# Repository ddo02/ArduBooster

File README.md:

# ArduBooster
TODO: Write the readme!

ArduBooster repository.

# License
This project is under dual-license.

First license is for commercial use of this project. To build a product, based on this project, and sell it.

Second license is for non-commercial use of this project. To build a sample, to personal use or education use.

# Donate

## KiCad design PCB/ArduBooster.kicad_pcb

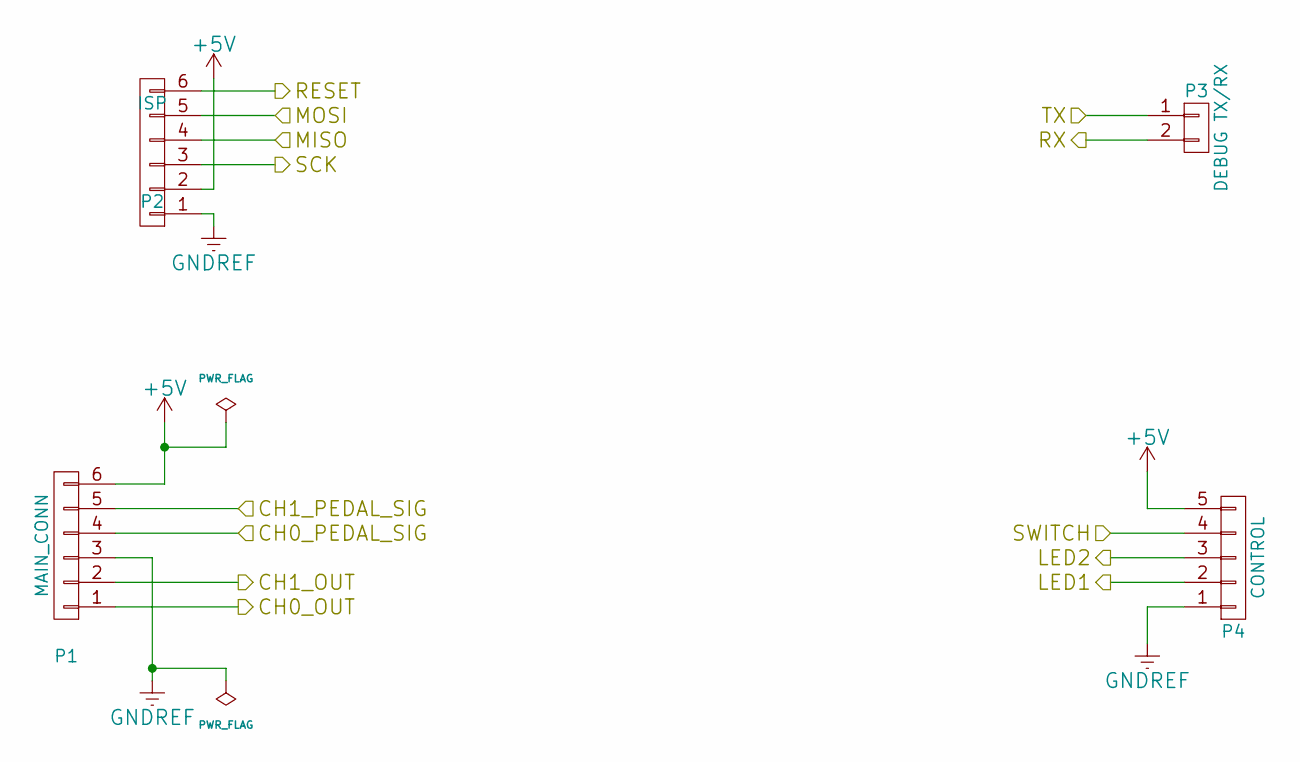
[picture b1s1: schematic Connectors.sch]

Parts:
P1: MAIN_CONN; Molex_MiniFit-JR-5569-06A1_2x03x4.20mm_Angled
P2: ISP; Pin_Header_Straight_1x06_Pitch2.54mm
P3: DEBUG TX/RX; Pin_Header_Straight_1x02_Pitch2.54mm
P4: CONTROL; Wafer_Horizontal15x5.8x7RM2.5-5

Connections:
+5V: P1.6, P2.2, P4.5; also elsewhere on the board
/Base Arduino/CH0_OUT: P1.1; also elsewhere on the board
/Base Arduino/CH0_PEDAL_SIG: P1.4; also elsewhere on the board
/Base Arduino/CH1_OUT: P1.2; also elsewhere on the board
/Base Arduino/CH1_PEDAL_SIG: P1.5; also elsewhere on the board
/Base Arduino/LED1: P4.2; also elsewhere on the board
/Base Arduino/LED2: P4.3; also elsewhere on the board
/Base Arduino/MISO: P2.4; also elsewhere on the board
/Base Arduino/MOSI: P2.5; also elsewhere on the board
/Base Arduino/RESET: P2.6; also elsewhere on the board
/Base Arduino/RX: P3.2; also elsewhere on the board
/Base Arduino/SCK: P2.3; also elsewhere on the board
/Base Arduino/SWITCH: P4.4; also elsewhere on the board
/Base Arduino/TX: P3.1; also elsewhere on the board
GNDREF: P1.3, P2.1, P4.1; also elsewhere on the board

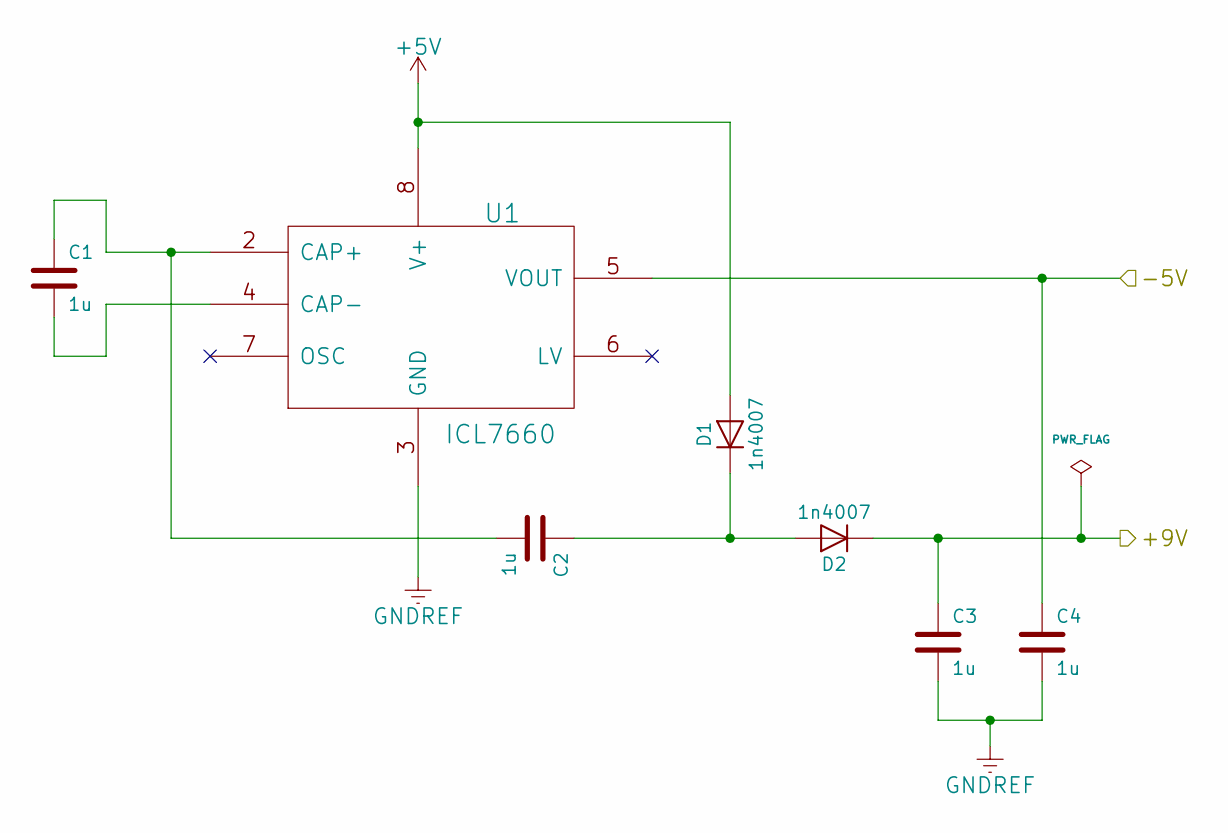
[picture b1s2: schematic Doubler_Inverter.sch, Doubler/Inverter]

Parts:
C1, C2, C3, C4: 1u; C_Rect_L7.0mm_W4.5mm_P5.00mm
D1, D2: 1n4007; D_A-405_P2.54mm_Vertical_AnodeUp
U1: ICL7660; DIP-8_W7.62mm_LongPads

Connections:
+5V: D1.2 (A), U1.8 (V+); also elsewhere on the board
/Doubler_Inverter/+9V: C3.1, D2.1 (K); also elsewhere on the board
/Doubler_Inverter/-5V: C4.1, U1.5 (VOUT); also elsewhere on the board
GNDREF: C3.2, C4.2, U1.3 (GND); also elsewhere on the board
unnamed: C1.1, C2.2, U1.2 (CAP+)
unnamed: C1.2, U1.4 (CAP-)
unnamed: C2.1, D1.1 (K), D2.2 (A)

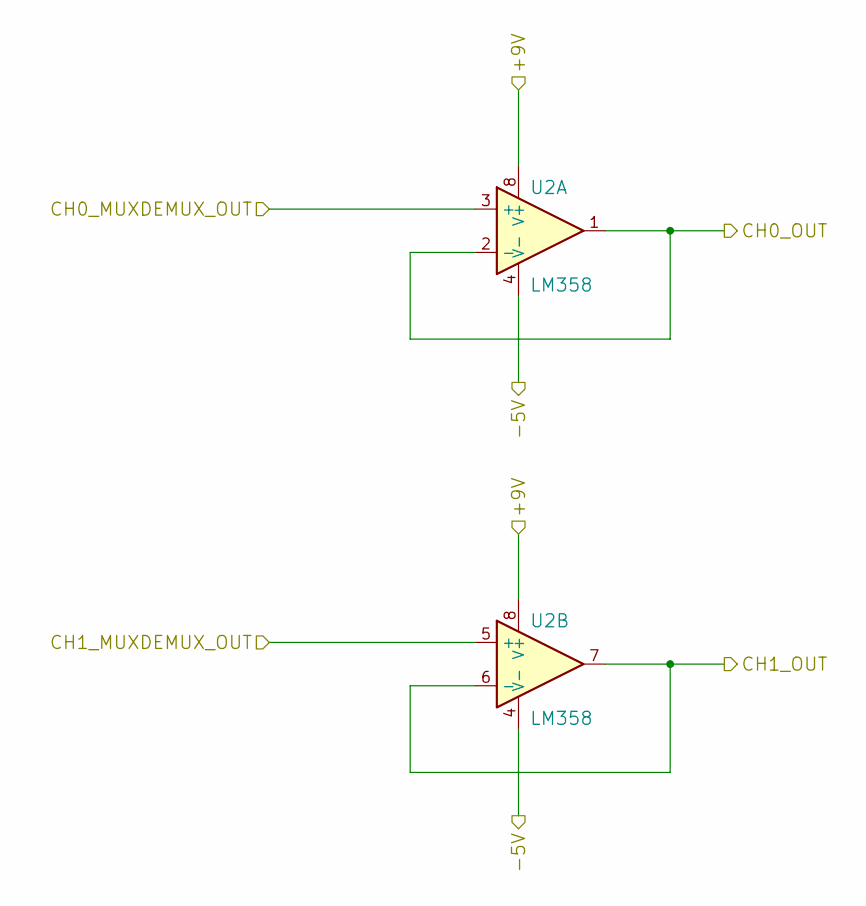
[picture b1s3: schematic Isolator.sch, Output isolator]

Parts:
U2: LM358; DIP-8_W7.62mm_LongPads

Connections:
/Base Arduino/CH0_OUT: U2.1, U2.2 (-); also elsewhere on the board
/Base Arduino/CH1_OUT: U2.6 (-), U2.7; also elsewhere on the board
/Doubler_Inverter/+9V: U2.8 (V+); also elsewhere on the board
/Doubler_Inverter/-5V: U2.4 (V-); also elsewhere on the board
/Isolator/CH0_MUXDEMUX_OUT: U2.3 (+); also elsewhere on the board
/Isolator/CH1_MUXDEMUX_OUT: U2.5 (+); also elsewhere on the board

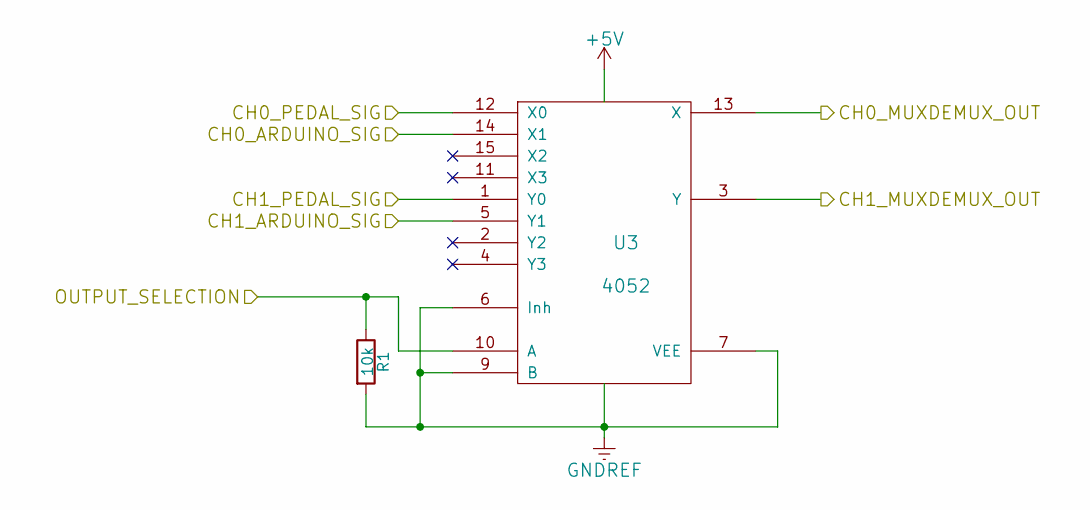
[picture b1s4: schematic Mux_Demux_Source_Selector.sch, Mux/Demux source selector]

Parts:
R1: 10k; R_Axial_DIN0207_L6.3mm_D2.5mm_P2.54mm_Vertical
U3: 4052; DIP-16_W7.62mm_LongPads

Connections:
+5V: U3.16 (VDD); also elsewhere on the board
/Base Arduino/CH0_ARDUINO_SIG: U3.14 (X1); also elsewhere on the board
/Base Arduino/CH0_PEDAL_SIG: U3.12 (X0); also elsewhere on the board
/Base Arduino/CH1_ARDUINO_SIG: U3.5 (Y1); also elsewhere on the board
/Base Arduino/CH1_PEDAL_SIG: U3.1 (Y0); also elsewhere on the board
/Base Arduino/MOSI: R1.1, U3.10 (A); also elsewhere on the board
/Isolator/CH0_MUXDEMUX_OUT: U3.13 (X); also elsewhere on the board
/Isolator/CH1_MUXDEMUX_OUT: U3.3 (Y); also elsewhere on the board
GNDREF: R1.2, U3.6 (Inh), U3.7 (VEE), U3.8 (VSS), U3.9 (B); also elsewhere on the board

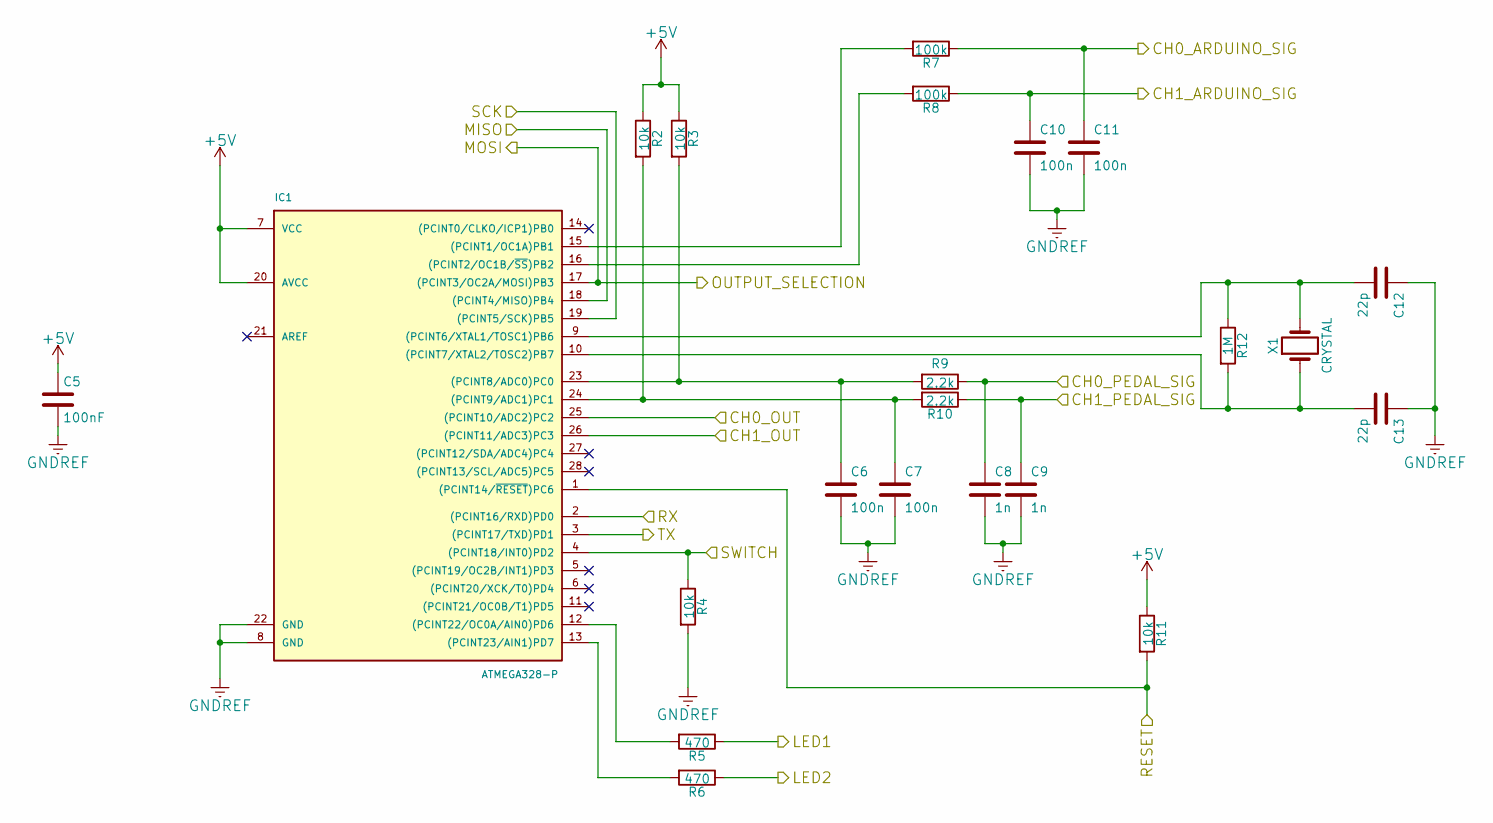
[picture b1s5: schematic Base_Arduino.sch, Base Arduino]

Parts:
C5: 100nF; C_Rect_L7.0mm_W2.5mm_P5.00mm
C6, C7, C10, C11: 100n; C_Rect_L7.0mm_W2.5mm_P5.00mm
C8, C9: 1n; C_Rect_L7.0mm_W2.0mm_P5.00mm
C12, C13: 22p; C_Rect_L7.0mm_W2.0mm_P5.00mm
IC1: ATMEGA328-P; DIP-28_W7.62mm_LongPads
R2, R3, R4, R11: 10k; R_Axial_DIN0207_L6.3mm_D2.5mm_P2.54mm_Vertical
R5, R6: 470; R_Axial_DIN0207_L6.3mm_D2.5mm_P2.54mm_Vertical
R7, R8: 100k; R_Axial_DIN0207_L6.3mm_D2.5mm_P2.54mm_Vertical
R9, R10: 2.2k; R_Axial_DIN0207_L6.3mm_D2.5mm_P7.62mm_Horizontal
R12: 1M; R_Axial_DIN0207_L6.3mm_D2.5mm_P2.54mm_Vertical
X1: CRYSTAL; Crystal_HC49-U_Vertical

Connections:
+5V: C5.1, IC1.7 (VCC), IC1.20 (AVCC), R2.1, R3.1, R11.1; also elsewhere on the board
/Base Arduino/CH0_ARDUINO_SIG: C11.1, R7.1; also elsewhere on the board
/Base Arduino/CH0_OUT: IC1.25 ((PCINT10/ADC2)PC2); also elsewhere on the board
/Base Arduino/CH0_PEDAL_SIG: C8.1, R9.1; also elsewhere on the board
/Base Arduino/CH1_ARDUINO_SIG: C10.1, R8.1; also elsewhere on the board
/Base Arduino/CH1_OUT: IC1.26 ((PCINT11/ADC3)PC3); also elsewhere on the board
/Base Arduino/CH1_PEDAL_SIG: C9.1, R10.1; also elsewhere on the board
/Base Arduino/LED1: R5.1; also elsewhere on the board
/Base Arduino/LED2: R6.1; also elsewhere on the board
/Base Arduino/MISO: IC1.18 ((PCINT4/MISO)PB4); also elsewhere on the board
/Base Arduino/MOSI: IC1.17 ((PCINT3/OC2A/MOSI)PB3); also elsewhere on the board
/Base Arduino/RESET: IC1.1 ((PCINT14/~RESET~)PC6), R11.2; also elsewhere on the board
/Base Arduino/RX: IC1.2 ((PCINT16/RXD)PD0); also elsewhere on the board
/Base Arduino/SCK: IC1.19 ((PCINT5/SCK)PB5); also elsewhere on the board
/Base Arduino/SWITCH: IC1.4 ((PCINT18/INT0)PD2), R4.1; also elsewhere on the board
/Base Arduino/TX: IC1.3 ((PCINT17/TXD)PD1); also elsewhere on the board
GNDREF: C5.2, C6.2, C7.2, C8.2, C9.2, C10.2, C11.2, C12.1, C13.1, IC1.8 (GND), IC1.22 (GND), R4.2; also elsewhere on the board
unnamed: C6.1, IC1.23 ((PCINT8/ADC0)PC0), R3.2, R9.2
unnamed: C7.1, IC1.24 ((PCINT9/ADC1)PC1), R2.2, R10.2
unnamed: C12.2, IC1.9 ((PCINT6/XTAL1/TOSC1)PB6), R12.1, X1.2
unnamed: C13.2, IC1.10 ((PCINT7/XTAL2/TOSC2)PB7), R12.2, X1.1
unnamed: IC1.12 ((PCINT22/OC0A/AIN0)PD6), R5.2
unnamed: IC1.13 ((PCINT23/AIN1)PD7), R6.2
unnamed: IC1.15 ((PCINT1/OC1A)PB1), R7.2
unnamed: IC1.16 ((PCINT2/OC1B/~SS~)PB2), R8.2

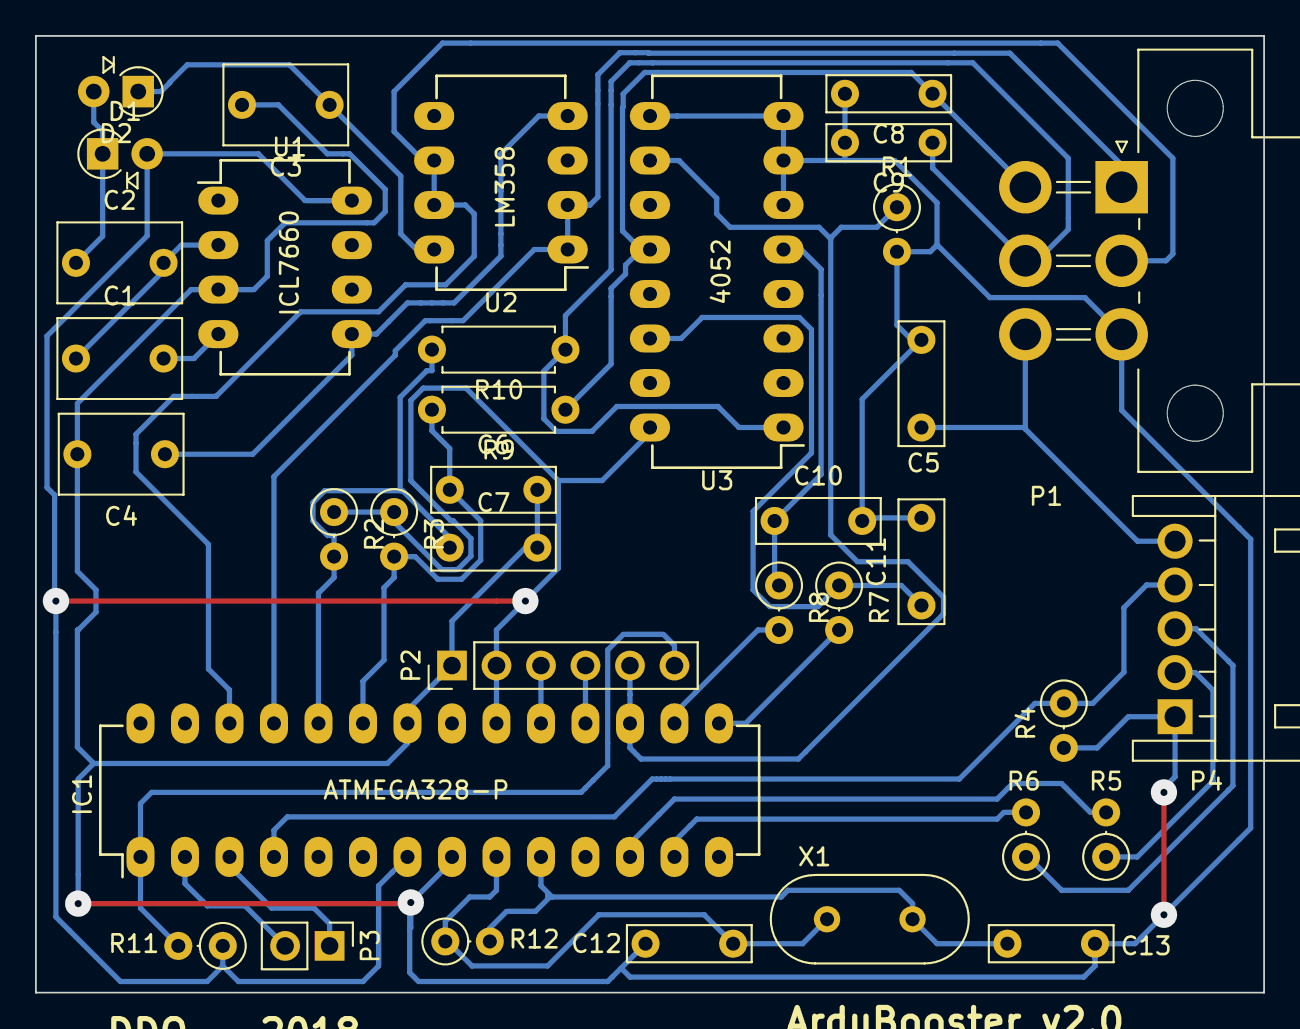
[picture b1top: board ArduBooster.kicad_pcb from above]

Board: 2 copper layers, 70.1 x 54.6 mm, 36 parts (0 on the bottom side), 32 nets.

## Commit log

2016-08-21 License file
2016-08-21 Rename LICENSE to LICENSE_commercial
2016-08-21 Rename LICENSE_commercial to LICENSE.commercial
2016-08-21 License draft
2016-08-21 New non commercial license.
2016-08-21 Formatting
2016-08-21 Commercial license
2016-08-21 License
2016-08-21 Initial Kicad project commit.
2016-08-21 Initial firmware commit.
2016-08-21 Study links
2016-08-22 Creating folder structure to work with Arduino IDE.
2016-08-22 TODO list Watchdog enabled (15ms) Blink leds at startup.
2016-08-22 Lower engineering margin :) (10% to 5% [?])
2016-08-23 Libraries and footprints adjustments. New connectors (4 pins main, 2 pins debug and 6 pins isp). New source input cap.
2016-08-24 New connectors connection. Labels corrections (direction).
2016-08-24 New connectors footprints. New .net file. New BoM file.
2016-08-24 Correct DIP sockets footprints.
2016-08-24 Correct footprint main connector.
2016-08-24 Initial new board route.
2016-08-24 First components placement.
2016-08-24 Routing...
2016-08-25 Output feedback.
2016-08-25 Optional crystal resistor.
2016-08-25 Resistor footprint.
2016-08-25 New crystal footprint. New route.
2016-08-26 Gerber and drill files
2016-08-26 New route, gerber files and drill files.
2016-08-26 Initial output feedback connection correction.
2016-08-27 Output feedback connection correction.
2016-09-04 Initial PID class.
2016-09-04 Initial PID.
2016-10-02 PID tests PWM 10-bit Debug mode
2016-10-02 Changed DAC resistor to 100k (to works fine with new 10-bit PWM and new frenquency[15khz])
2016-10-13 ADC tests.
2016-10-14 ADC interrupt
2016-10-18 Min output correction.
2016-10-27 Find sensor type
2016-11-04 Added digital filter (from https://github.com/JonHub/Filters)
2017-04-02 Changed minimum throttle from 5% to 7%. DSP removed. Added a timer to start conversions. To wait output RC filter start.
2017-08-19 ADC corrections tests.
2018-01-07 Last commit before Mux/Demux removel. Single layer PCB incompete (3 wires). Add ADC input filter.
